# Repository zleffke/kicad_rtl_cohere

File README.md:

# KiCAD PCBs For RTL-SDR Coherent Receiver Projects
KiCAD projects for RTL-SDR coherency projects

## Board Descriptions
| Board | Description |
| --- | --- |
| clk_dist_4chan | 4 channel clock distribution |
| clk_dist_8chan | 8 channel clock distribution |
| external_clock | External clock interface to RTL-SDR V3 header |
| rf_split | 4 channel rf splitter for calibration noise distribution, two versions |

### Credit where its due!
This project is heavily inspired by the awesome work at [coherent-receiver.com](https://coherent-receiver.com).
I plan to make use of some common features, but also plan to do my own customized PCB layouts.
My work will be nowhere near as professional as theirs.
I highly recommend interested readers check out their page.

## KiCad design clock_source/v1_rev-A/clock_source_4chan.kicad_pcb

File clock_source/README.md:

# Clock Source Board
For coherent RTL-SDR projects.  
Based on Temperature Controlled Crystal Oscillator (TCXO).  
4 Channel Clock source (fanout) board
28.8 MHz clock frequency to RTL-SDR V3.

## V1 - 4 Channel Clock Source
- TCXO:  [Connor Winfield B31 28.8 MHz TCXO](http://www.conwin.com/datasheets/tx/tx415.pdf).
  - +-500 ppb
  - 2.0x2.5 mm footprint
  - digikey:  https://www.digikey.com/en/products/detail/connor-winfield/B31-028-8M/10296363
  
- SN74LVC2G14 buffer.  Matches ~10kOhm impedance of TCXO to 50 Ohm impedance of 5PB1104PGxx,
- Based on the 5PB1104PGxx Clock fanout buffer.
- UFL Connectors, to match the external clock interface board of the RTL SDR V3.
- Integrated 35 MHz LPFs on out and bypassable LPF on input.

### Rev-A, 20220314
Rectified deficiencies identified in Rev-.

### Rev-, 20220304
Forgot two key components:
- AC coupling capacitor at output of TCXO circuit.
- Resistor in parallel across input/output of SN74LVC2G14.
- Tested with razor blade / blue wire version of board.

### REMINDER! Credit where its due!
This project is heavily inspired by the awesome work at [coherent-receiver.com](https://coherent-receiver.com).

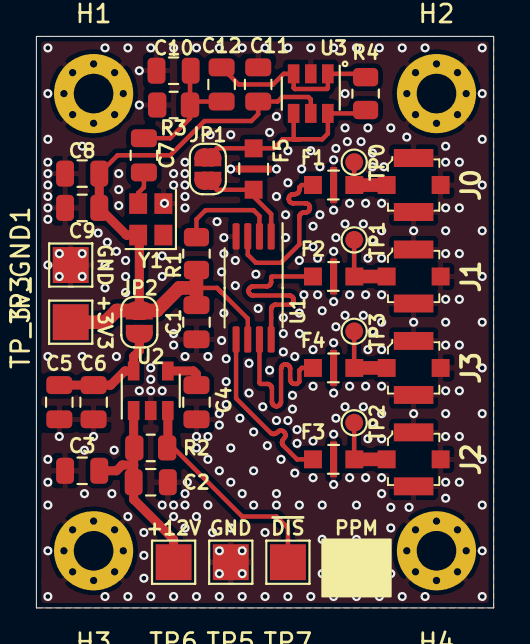
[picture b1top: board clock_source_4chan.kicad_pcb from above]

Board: 2 copper layers, 25.4 x 31.8 mm, 44 parts (0 on the bottom side), 20 nets.

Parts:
C1, C3, C4, C6, C8, C11: 0.1uF; C_0805_2012Metric
C2: 1uF; C_0805_2012Metric
C5: 10uF; C_0805_2012Metric
C7, C12: 1000pF; C_0805_2012Metric
C9: 0.01uF; C_0805_2012Metric
C10: 10pF; C_0805_2012Metric
F1, F2, F3, F4, F5: MEM2012S35R0T001; 0805_3PC_Pad
H1, H2, H3, H4: MountingHole_Pad; MountingHole_2.2mm_M2_Pad_Via
J0: Y0; Molex_734120114_UMC_RF_CONN_Vertical
J1: Y1; Molex_734120114_UMC_RF_CONN_Vertical
J2: Y2; Molex_734120114_UMC_RF_CONN_Vertical
J3: Y3; Molex_734120114_UMC_RF_CONN_Vertical
JP1: CLKIN_FILT_BYPASS; SolderJumper-2_P1.3mm_Open_RoundedPad1.0x1.5mm
JP2: VREG; SolderJumper-2_P1.3mm_Open_RoundedPad1.0x1.5mm
R1, R2: 100k; R_0805_2012Metric
R3, R4: 10k; R_0805_2012Metric
TP0, TP1, TP2, TP3: TestPoint; TestPoint_Pad_D1.0mm
TP5, TP6, TP7: TestPoint; TestPoint_Pad_2.0x2.0mm
TP_3v3: TestPoint; TestPoint_Pad_2.0x2.0mm
TP_GND1: TestPoint; TestPoint_Pad_2.0x2.0mm
U1: 5PB1104PGxx; TSSOP-8_4.4x3mm_P0.65mm
U2: SPX3819M5-L-3-3; SOT-23-5
U3: SN74LVC2G14DBV; SOT-23-6
Y1: TCXO_B31; Crystal_SMD_2520-4Pin_2.5x2.0mm

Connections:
+3V3: C1.2, C8.1, C9.1, C11.1, JP2.2, R1.2, TP_3v3.1, U1.6, U3.5, Y1.4
+12V: C2.1, C3.1, R2.1, TP6.1, U2.1
/Y0: F1.1, U1.3
/Y1: F2.1, U1.8
/Y2: F3.1, U1.5
/Y3: F4.1, U1.7
GND: C1.1, C2.2, C3.2, C4.2, C5.2, C6.2, C8.2, C9.2, C10.2, C11.2, F1.3, F2.3, F3.3, F4.3, F5.3, H1.1, H2.1, H3.1, H4.1, J0.1, J1.1, J2.1, J3.1, R3.2, TP5.1, TP_GND1.1, U1.4, U2.2, U3.2, Y1.2
unnamed: C4.1, U2.4
unnamed: C5.1, C6.1, JP2.1, U2.5
unnamed: C7.1, Y1.3
unnamed: C7.2, C10.1, C12.2, R3.1
unnamed: C12.1, R4.2, U3.1, U3.3
unnamed: F1.2, J0.2, TP0.1
unnamed: F2.2, J1.2, TP1.1
unnamed: F3.2, J2.2, TP2.1
unnamed: F4.2, J3.2, TP3.1
unnamed: F5.1, JP1.1, R4.1, U3.4, U3.6
unnamed: F5.2, JP1.2, U1.1
unnamed: R1.1, U1.2
unnamed: R2.2, TP7.1, U2.3

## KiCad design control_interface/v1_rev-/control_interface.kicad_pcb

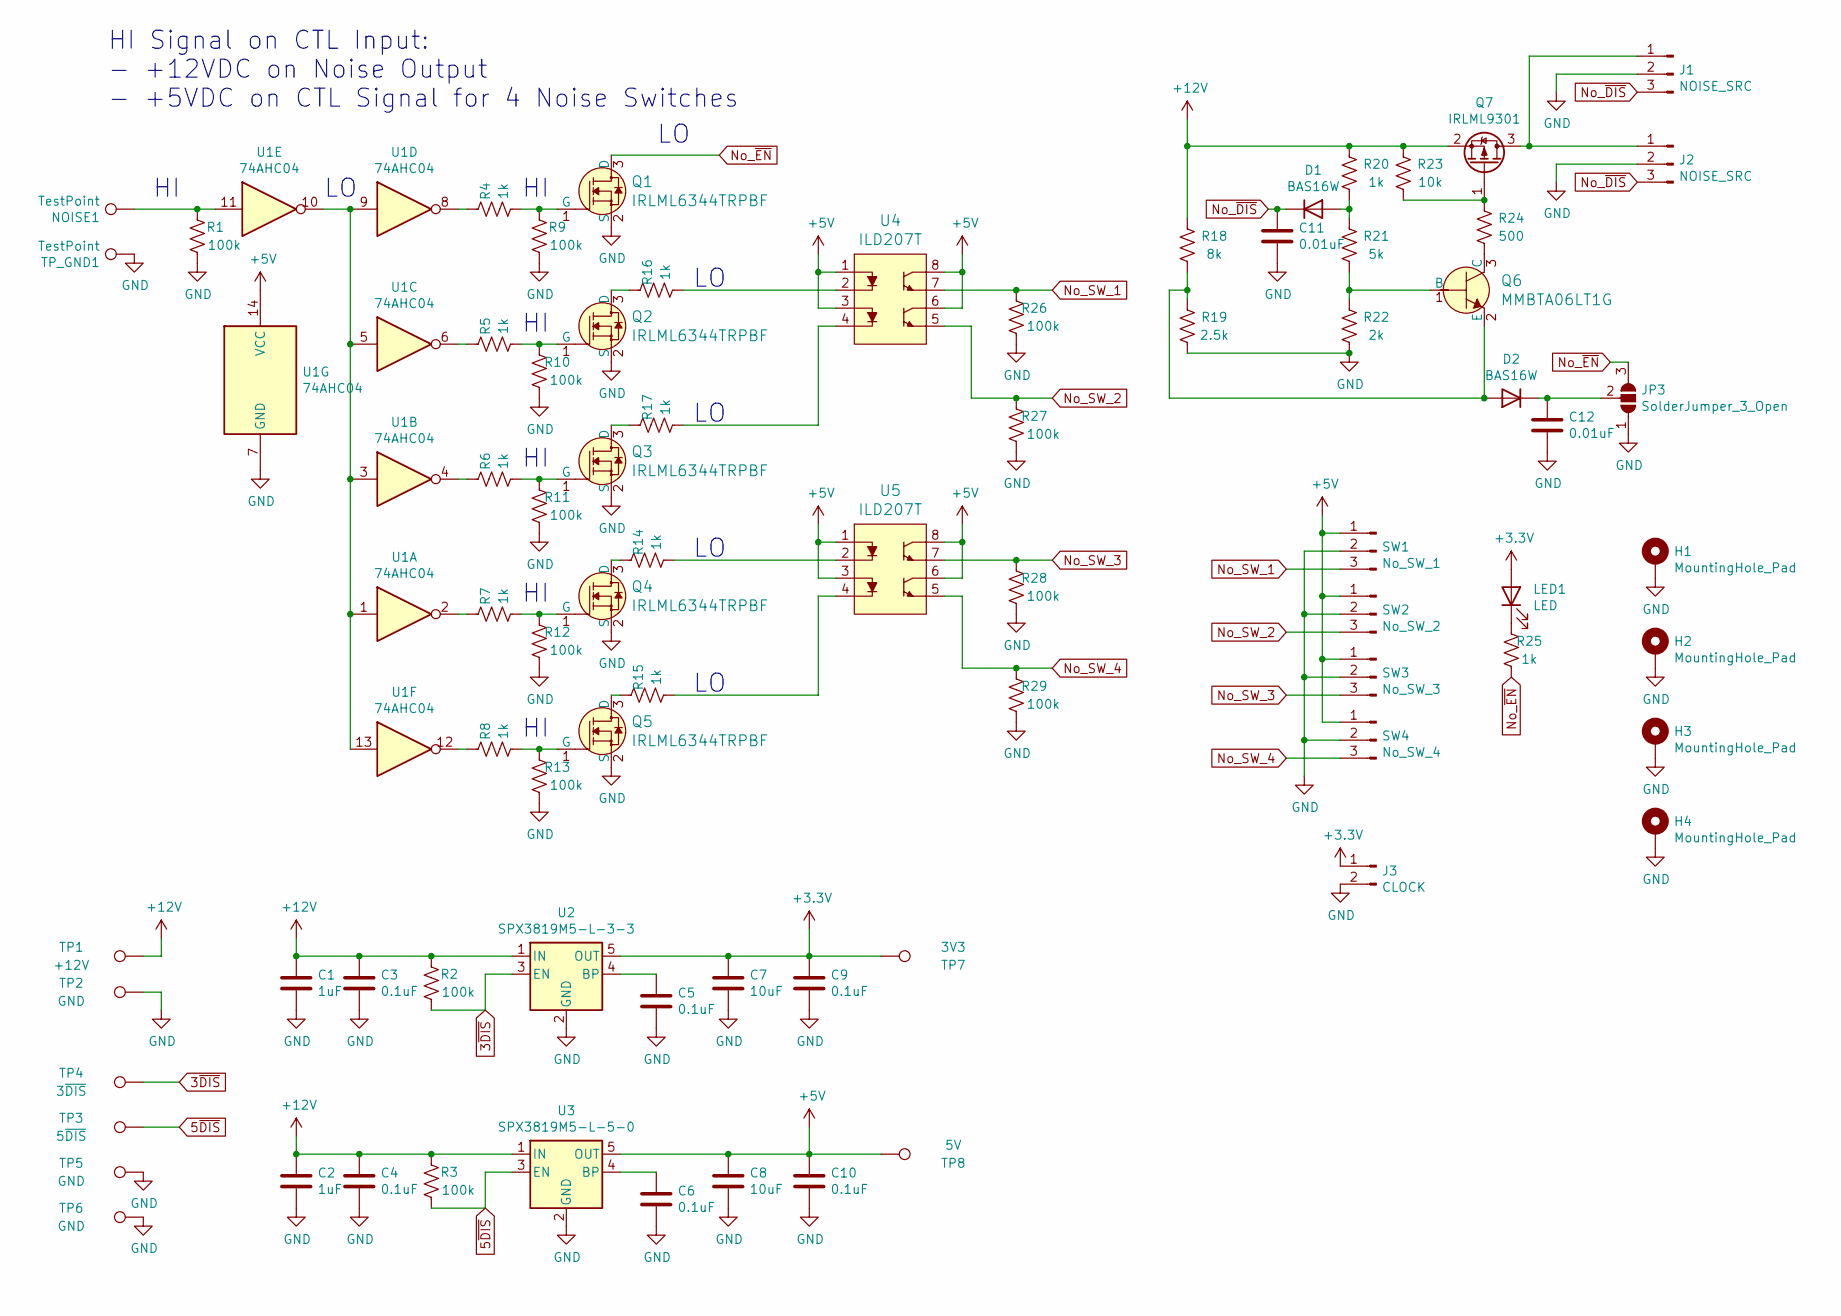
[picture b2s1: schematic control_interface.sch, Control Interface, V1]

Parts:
C1, C2: 1uF; C_0805_2012Metric
C3, C4, C5, C6, C9, C10: 0.1uF; C_0805_2012Metric
C7, C8: 10uF; C_0805_2012Metric
C11, C12: 0.01uF; C_0805_2012Metric
D1, D2: BAS16W; SOT-323_SC-70
H1, H2, H3, H4: MountingHole_Pad; MountingHole_2.2mm_M2_Pad_Via
J1, J2: NOISE_SRC; PinHeader_1x03_P2.54mm_Vertical
J3: CLOCK; PinHeader_1x02_P2.54mm_Vertical
JP3: SolderJumper_3_Open; SolderJumper-3_P1.3mm_Open_RoundedPad1.0x1.5mm_NumberLabels
LED1: LED; LED_0805_2012Metric
NOISE1: TestPoint; TestPoint_Pad_2.0x2.0mm
Q1, Q2, Q3, Q4, Q5: IRLML6344TRPBF; SOT-23-3; MPN IRLML6344TRPBF; Digi-Key_PN IRLML6344TRPBFCT-ND
Q6: MMBTA06LT1G; SOT-23-3; MPN MMBTA06LT1G; Digi-Key_PN MMBTA06LT1GOSCT-ND
Q7: IRLML9301; SOT-23-3
R1, R2, R3, R9, R10, R11, R12, R13, R26, R27, R28, R29: 100k; R_0805_2012Metric
R4, R5, R6, R7, R8, R14, R15, R16, R17, R20, R25: 1k; R_0805_2012Metric
R18: 8k; R_0805_2012Metric
R19: 2.5k; R_0805_2012Metric
R21: 5k; R_0805_2012Metric
R22: 2k; R_0805_2012Metric
R23: 10k; R_0805_2012Metric
R24: 500; R_0805_2012Metric
SW1: No_SW_1; PinHeader_1x03_P2.54mm_Vertical
SW2: No_SW_2; PinHeader_1x03_P2.54mm_Vertical
SW3: No_SW_3; PinHeader_1x03_P2.54mm_Vertical
SW4: No_SW_4; PinHeader_1x03_P2.54mm_Vertical
TP1: +12V; TestPoint_Pad_2.0x2.0mm
TP2, TP5, TP6: GND; TestPoint_Pad_2.0x2.0mm
TP3: 5~DIS; TestPoint_Pad_2.0x2.0mm
TP4: 3~DIS; TestPoint_Pad_2.0x2.0mm
TP7: 3V3; TestPoint_Pad_2.0x2.0mm
TP8: 5V; TestPoint_Pad_2.0x2.0mm
TP_GND1: TestPoint; TestPoint_Pad_2.0x2.0mm
U1: 74AHC04; SOIC-14_W3.9mm
U2: SPX3819M5-L-3-3; SOT-23-5
U3: SPX3819M5-L-5-0; SOT-23-5
U4, U5: ILD207T; SOIC-8_W3.9mm; MPN ILD207T; Digi-Key_PN 751-1310-1-ND

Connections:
3~DIS: R2.2, TP4.1, U2.3 (EN)
5~DIS: R3.2, TP3.1, U3.3 (EN)
+3V3: C7.1, C9.1, J3.1, LED1.2 (A), TP7.1, U2.5 (OUT)
+5V: C8.1, C10.1, SW1.1, SW2.1, SW3.1, SW4.1, TP8.1, U1.14 (VCC), U3.5 (OUT), U4.1, U4.3, U4.6, U4.8, U5.1, U5.3, U5.6, U5.8
+12V: C1.1, C2.1, C3.1, C4.1, Q7.2 (S), R2.1, R3.1, R18.1, R20.1, R23.1, TP1.1, U2.1 (IN), U3.1 (IN)
GND: C1.2, C2.2, C3.2, C4.2, C5.2, C6.2, C7.2, C8.2, C9.2, C10.2, C11.2, C12.2, H1.1, H2.1, H3.1, H4.1, J1.2, J2.2, J3.2, JP3.1 (A), Q1.2 (S), Q2.2 (S), Q3.2 (S), Q4.2 (S), Q5.2 (S), R1.2, R9.2, R10.2, R11.2, R12.2, R13.2, R19.2, R22.2, R26.2, R27.2, R28.2, R29.2, SW1.2, SW2.2, SW3.2, SW4.2, TP2.1, TP5.1, TP6.1, TP_GND1.1, U1.7 (GND), U2.2 (GND), U3.2 (GND)
unnamed: C5.1, U2.4 (BP)
unnamed: C6.1, U3.4 (BP)
unnamed: C12.1, D2.3 (K), JP3.2 (C)
unnamed: D1.1 (A), R20.2, R21.1
unnamed: D2.1 (A), Q6.2 (E), R18.2, R19.1
unnamed: J1.1, J2.1, Q7.3 (D)
unnamed: LED1.1 (K), R25.1
unnamed: NOISE1.1, R1.1, U1.11
unnamed: Q1.1 (G), R4.2, R9.1
unnamed: Q2.1 (G), R5.2, R10.1
unnamed: Q2.3 (D), R16.1
unnamed: Q3.1 (G), R6.2, R11.1
unnamed: Q3.3 (D), R17.1
unnamed: Q4.1 (G), R7.2, R12.1
unnamed: Q4.3 (D), R14.1
unnamed: Q5.1 (G), R8.2, R13.1
unnamed: Q5.3 (D), R15.1
unnamed: Q6.1 (B), R21.2, R22.1
unnamed: Q6.3 (C), R24.2
unnamed: Q7.1 (G), R23.2, R24.1
unnamed: R4.1, U1.8
unnamed: R5.1, U1.6
unnamed: R6.1, U1.4
unnamed: R7.1, U1.2
unnamed: R8.1, U1.12
unnamed: R14.2, U5.2
unnamed: R15.2, U5.4
unnamed: R16.2, U4.2
unnamed: R17.2, U4.4
unnamed: U1.1, U1.3, U1.5, U1.9, U1.10, U1.13
No_SW_1: R26.1, SW1.3, U4.7
No_SW_2: R27.1, SW2.3, U4.5
No_SW_3: R28.1, SW3.3, U5.7
No_SW_4: R29.1, SW4.3, U5.5
No_~DIS: C11.1, D1.3 (K), J1.3, J2.3
No_~EN: JP3.3 (B), Q1.3 (D), R25.2

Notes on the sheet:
HI Signal on CTL Input: - +12VDC on Noise Output - +5VDC on CTL Signal for 4 Noise Switches

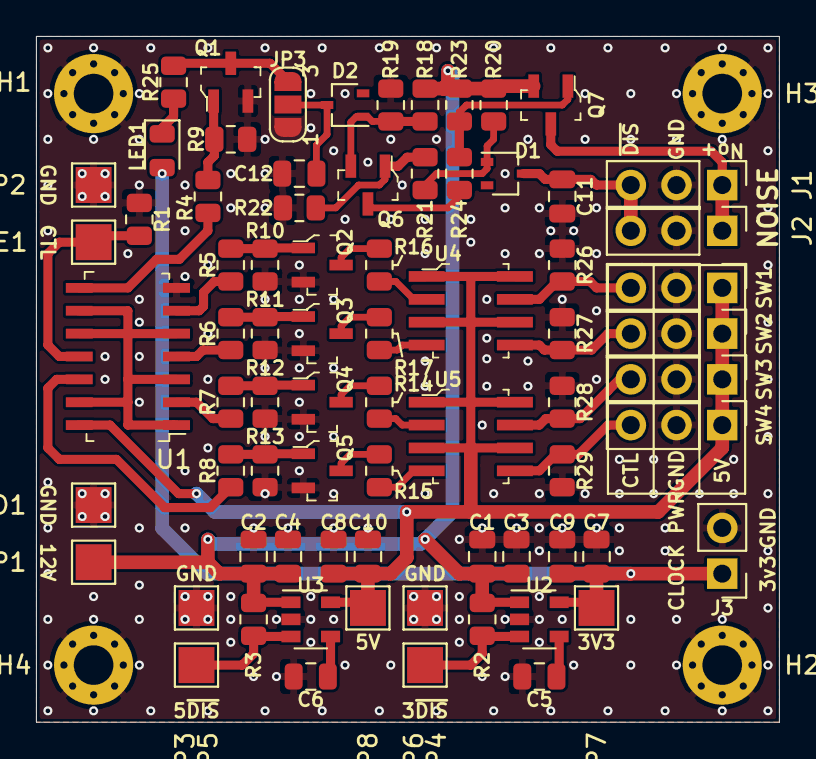
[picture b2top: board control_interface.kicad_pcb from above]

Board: 2 copper layers, 41.3 x 38.1 mm, 78 parts (0 on the bottom side), 42 nets.

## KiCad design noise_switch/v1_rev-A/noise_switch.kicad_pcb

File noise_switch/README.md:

# KiCAD PCBs For RTL-SDR Coherent Receiver Projects
Noise injection switch.  For injecting noise calibration signal into receive path.

## Board Descriptions
| Board | Description |
| --- | --- |
| V2, REV-  | Absorbative Switch.  MASW-007935-TR3000 design (uses SOT26 footprint).  Includes fix for SMA Connectors. |
| V1, REV-A | Reflective Switch.  MASWSS0136 design (uses SC70-6 footprint).  Fixed SMA Connector footprint to expose more copper. Update DC block capacitors to 1000pf.|
| V1, REV-  | Reflective Switch.  MASWSS0136 design (uses SC70-6 footprint) |

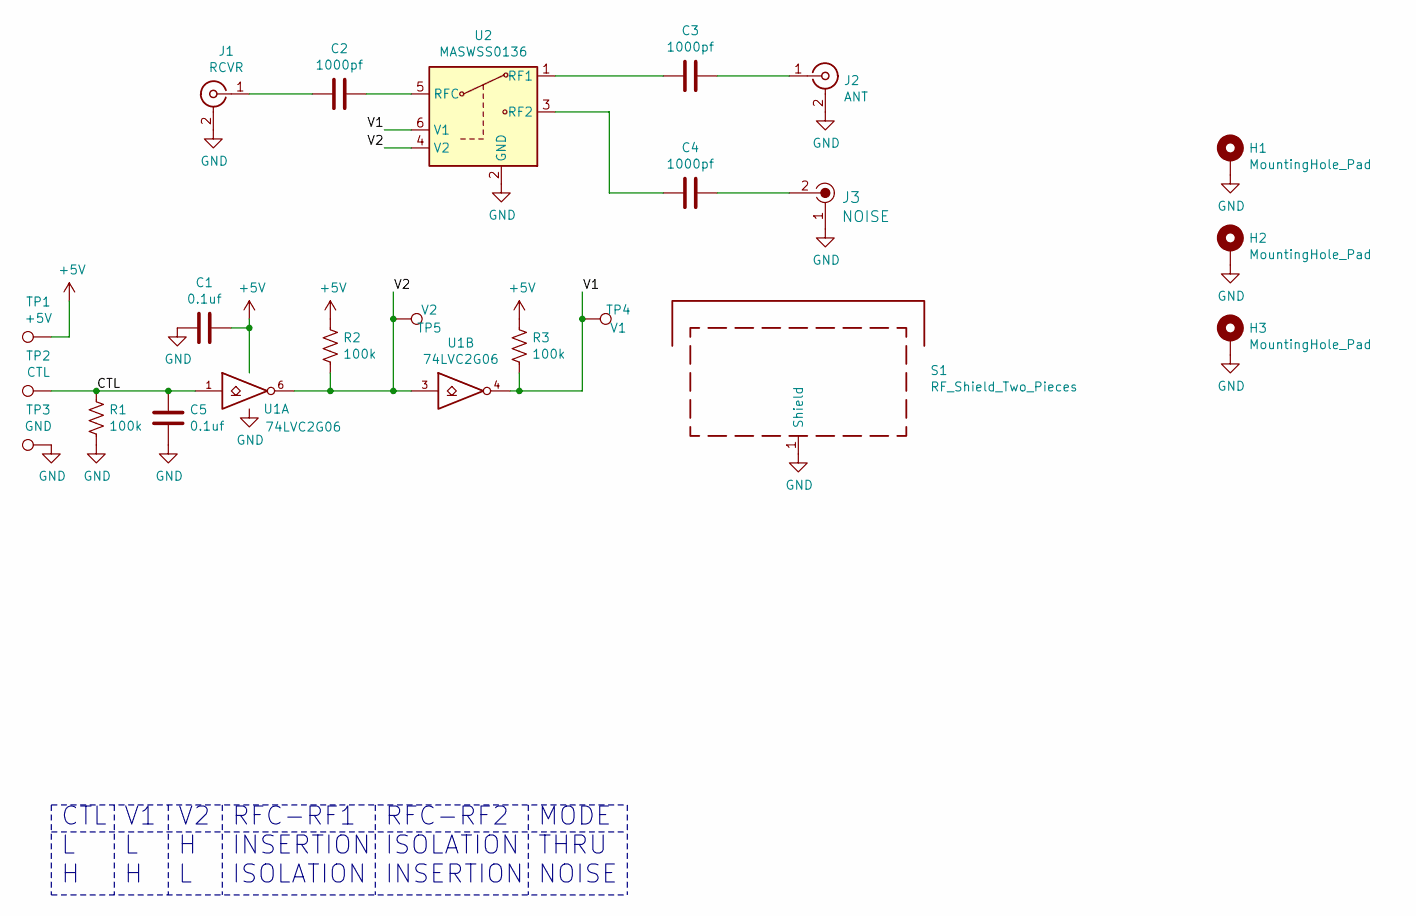
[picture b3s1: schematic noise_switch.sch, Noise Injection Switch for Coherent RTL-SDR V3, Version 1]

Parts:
C1, C5: 0.1uf; 0805
C2, C3, C4: 1000pf; 0805
H1, H2, H3: MountingHole_Pad; MountingHole_2.2mm_M2_Pad_Via
J1: RCVR; CONSMA013.062
J2: ANT; CONSMA003.062
J3: NOISE; Molex_734120114_UMC_RF_CONN_Vertical; MPN 0734120114; Digi-Key_PN WM3894CT-ND
R1, R2, R3: 100k; 0805
S1: RF_Shield_Two_Pieces; Wuerth_36103205_20x20mm
TP1: +5V; TestPoint_Pad_2.5x2.5mm
TP2: CTL; TestPoint_Pad_2.5x2.5mm
TP3: GND; TestPoint_Pad_2.5x2.5mm
TP4: V1; TestPoint_Pad_D1.5mm
TP5: V2; TestPoint_Pad_D1.5mm
U1: 74LVC2G06; SOT-363_SC-70-6
U2: MASWSS0136; SOT-363_SC-70-6

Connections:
+5V: C1.1, R2.1, R3.1, TP1.1, U1.5 (VCC)
/CTL: C5.2, R1.1, TP2.1, U1.1
/V1: R3.2, TP4.1, U1.4, U2.6 (V1)
/V2: R2.2, TP5.1, U1.3, U1.6, U2.4 (V2)
GND: C1.2, C5.1, H1.1, H2.1, H3.1, J1.2 (Ext), J2.2 (Ext), J3.1, R1.2, S1.1, TP3.1, U1.2 (GND), U2.2 (GND)
unnamed: C2.1, U2.5 (RFC)
unnamed: C2.2, J1.1 (In)
unnamed: C3.1, J2.1 (In)
unnamed: C3.2, U2.1 (RF1)
unnamed: C4.1, J3.2
unnamed: C4.2, U2.3 (RF2)

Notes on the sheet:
V2 H L
RFC-RF1 INSERTION ISOLATION
RFC-RF2 ISOLATION INSERTION
CTL L H
V1 L H
MODE THRU NOISE

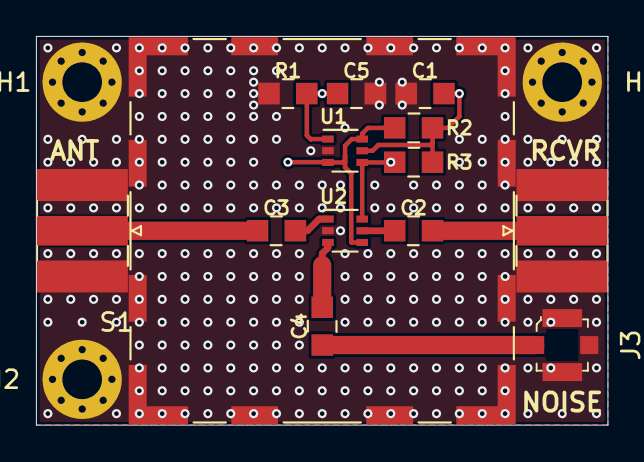
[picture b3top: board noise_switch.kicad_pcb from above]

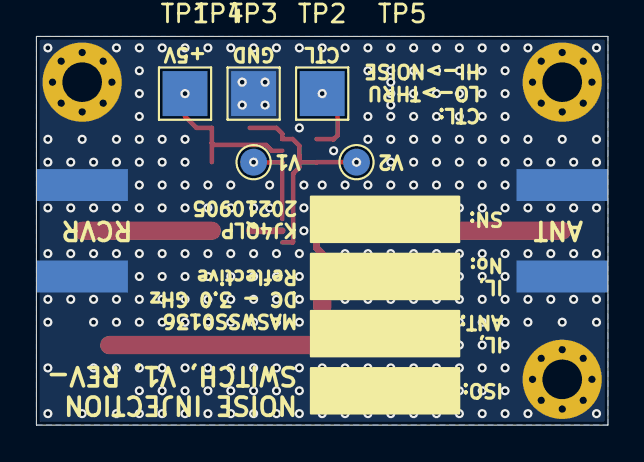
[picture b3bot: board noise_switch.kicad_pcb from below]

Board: 2 copper layers, 31.8 x 21.6 mm, 22 parts (5 on the bottom side), 11 nets.

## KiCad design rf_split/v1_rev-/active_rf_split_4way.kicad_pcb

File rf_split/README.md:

# Active RF Splitter Board Designs
- Primary use: distributing noise calibration source
- Given primary use, must try to control amplitude and phase to be equal on all outputs.
- Active because we are using RF amplifiers to overcome splitter losses.
  
## Board Versions

### Version 1 - Wye splitter
- based on 4-way Wye resistive splitter configuration
  - wye splitter is lossy, burns up half the power in the resistors.
  - 12dB loss from splitter input to output (for 4 channel).
- Active 4 channel noise distribution.
- BGA2815 RF amplifier from NXP (first time trying).

### Version 2 - Minicircuits splitter
- Nearly identical to Version 1, but based on cascaded minicircuits [TCP-2-25X+](https://www.minicircuits.com/WebStore/dashboard.html?model=TCP-2-25X%2B) rf splitter.
- Active 4 channel noise distribution.
- BGA2815 RF amplifier from NXP (first time trying).

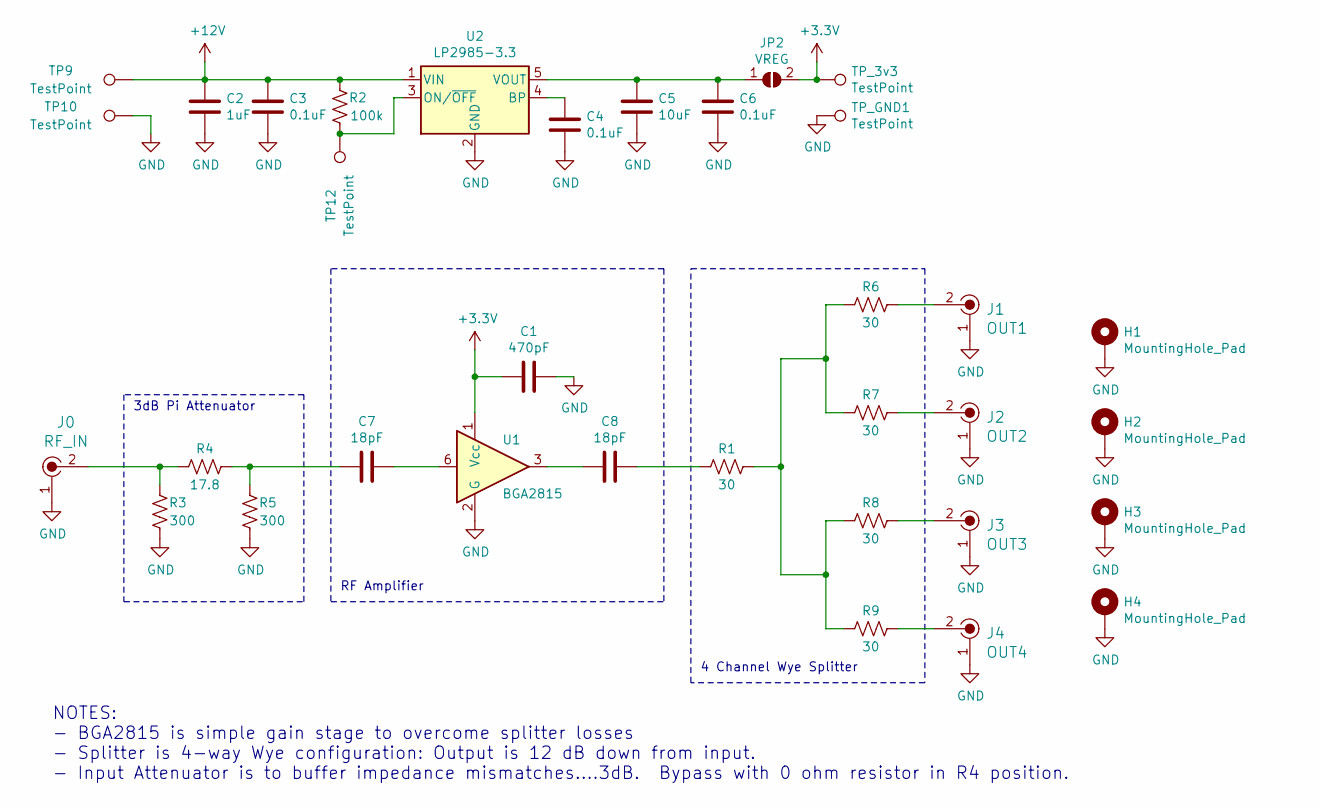
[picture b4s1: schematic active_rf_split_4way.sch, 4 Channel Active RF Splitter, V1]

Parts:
C1: 470pF; C_0805_2012Metric
C2: 1uF; C_0805_2012Metric
C3, C4, C6: 0.1uF; C_0805_2012Metric
C5: 10uF; C_0805_2012Metric
C7, C8: 18pF; C_0805_2012Metric
H1, H2, H3, H4: MountingHole_Pad; MountingHole_2.2mm_M2_Pad_Via
J0: RF_IN; Molex_734120114_UMC_RF_CONN_Vertical; MPN 0734120114; Digi-Key_PN WM3894CT-ND
J1: OUT1; Molex_734120114_UMC_RF_CONN_Vertical; MPN 0734120114; Digi-Key_PN WM3894CT-ND
J2: OUT2; Molex_734120114_UMC_RF_CONN_Vertical; MPN 0734120114; Digi-Key_PN WM3894CT-ND
J3: OUT3; Molex_734120114_UMC_RF_CONN_Vertical; MPN 0734120114; Digi-Key_PN WM3894CT-ND
J4: OUT4; Molex_734120114_UMC_RF_CONN_Vertical; MPN 0734120114; Digi-Key_PN WM3894CT-ND
JP2: VREG; SolderJumper-2_P1.3mm_Open_RoundedPad1.0x1.5mm
R1, R6, R7, R8, R9: 30; R_0805_2012Metric
R2: 100k; R_0805_2012Metric
R3, R5: 300; R_0805_2012Metric
R4: 17.8; R_0805_2012Metric
TP9, TP10, TP12: TestPoint; TestPoint_Pad_2.0x2.0mm
TP_3v3: TestPoint; TestPoint_Pad_2.0x2.0mm
TP_GND1: TestPoint; TestPoint_Pad_2.0x2.0mm
U1: BGA2815; SOT-363_SC-70-6
U2: LP2985-3.3; SOT-23-5

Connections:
+3V3: C1.2, JP2.2 (B), TP_3v3.1, U1.1 (Vcc)
+12V: C2.1, C3.1, R2.1, TP9.1, U2.1 (VIN)
GND: C1.1, C2.2, C3.2, C4.2, C5.2, C6.2, H1.1, H2.1, H3.1, H4.1, J0.1, J1.1, J2.1, J3.1, J4.1, R3.2, R5.2, TP10.1, TP_GND1.1, U1.2 (G), U1.4 (G), U1.5 (G), U2.2 (GND)
unnamed: C4.1, U2.4 (BP)
unnamed: C5.1, C6.1, JP2.1 (A), U2.5 (VOUT)
unnamed: C7.1, U1.6
unnamed: C7.2, R4.2, R5.1
unnamed: C8.1, R1.1
unnamed: C8.2, U1.3
unnamed: J0.2, R3.1, R4.1
unnamed: J1.2, R6.2
unnamed: J2.2, R7.2
unnamed: J3.2, R8.2
unnamed: J4.2, R9.2
unnamed: R1.2, R6.1, R7.1, R8.1, R9.1
unnamed: R2.2, TP12.1, U2.3 (ON/~OFF~)

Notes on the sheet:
NOTES: - BGA2815 is simple gain stage to overcome splitter losses - Splitter is 4-way Wye configuration: Output is 12 dB down from input. - Input Attenuator is to buffer impedance mismatches....3dB. Bypass with 0 ohm resistor in R4 position.
4 Channel Wye Splitter
RF Amplifier
3dB Pi Attenuator

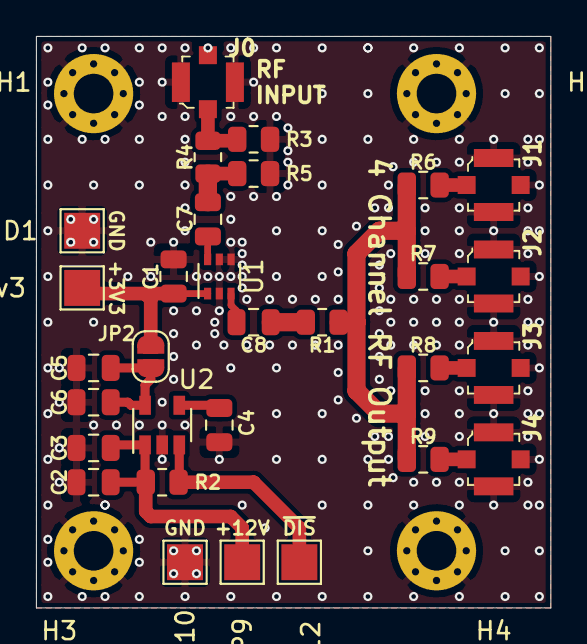
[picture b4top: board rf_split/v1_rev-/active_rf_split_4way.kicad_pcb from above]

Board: 2 copper layers, 28.6 x 31.8 mm, 34 parts (0 on the bottom side), 16 nets.

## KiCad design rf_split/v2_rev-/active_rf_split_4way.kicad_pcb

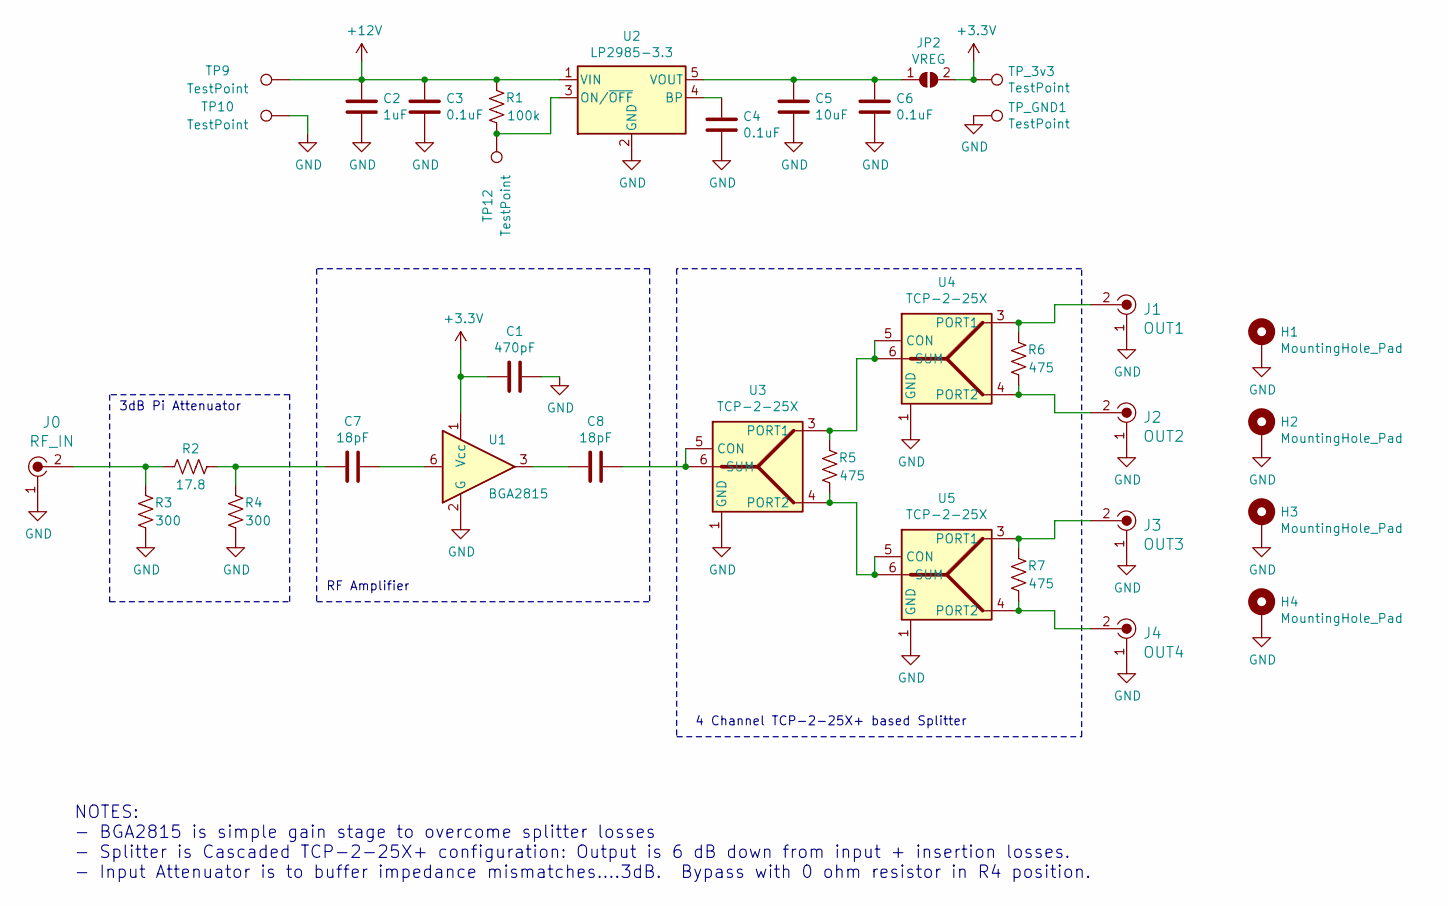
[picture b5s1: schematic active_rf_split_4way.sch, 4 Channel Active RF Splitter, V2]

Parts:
C1: 470pF; C_0805_2012Metric
C2: 1uF; C_0805_2012Metric
C3, C4, C6: 0.1uF; C_0805_2012Metric
C5: 10uF; C_0805_2012Metric
C7, C8: 18pF; C_0805_2012Metric
H1, H2, H3, H4: MountingHole_Pad; MountingHole_2.2mm_M2_Pad_Via
J0: RF_IN; Molex_734120114_UMC_RF_CONN_Vertical; MPN 0734120114; Digi-Key_PN WM3894CT-ND
J1: OUT1; Molex_734120114_UMC_RF_CONN_Vertical; MPN 0734120114; Digi-Key_PN WM3894CT-ND
J2: OUT2; Molex_734120114_UMC_RF_CONN_Vertical; MPN 0734120114; Digi-Key_PN WM3894CT-ND
J3: OUT3; Molex_734120114_UMC_RF_CONN_Vertical; MPN 0734120114; Digi-Key_PN WM3894CT-ND
J4: OUT4; Molex_734120114_UMC_RF_CONN_Vertical; MPN 0734120114; Digi-Key_PN WM3894CT-ND
JP2: VREG; SolderJumper-2_P1.3mm_Open_RoundedPad1.0x1.5mm
R1: 100k; R_0805_2012Metric
R2: 17.8; R_0805_2012Metric
R3, R4: 300; R_0805_2012Metric
R5, R6, R7: 475; R_0805_2012Metric
TP9, TP10, TP12: TestPoint; TestPoint_Pad_2.0x2.0mm
TP_3v3: TestPoint; TestPoint_Pad_2.0x2.0mm
TP_GND1: TestPoint; TestPoint_Pad_2.0x2.0mm
U1: BGA2815; SOT-363_SC-70-6
U2: LP2985-3.3; SOT-23-5
U3, U4, U5: TCP-2-25X; Mini-Circuits_DB1627

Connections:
+3V3: C1.2, JP2.2 (B), TP_3v3.1, U1.1 (Vcc)
+12V: C2.1, C3.1, R1.1, TP9.1, U2.1 (VIN)
GND: C1.1, C2.2, C3.2, C4.2, C5.2, C6.2, H1.1, H2.1, H3.1, H4.1, J0.1, J1.1, J2.1, J3.1, J4.1, R3.2, R4.2, TP10.1, TP_GND1.1, U1.2 (G), U1.4 (G), U1.5 (G), U2.2 (GND), U3.1 (GND), U4.1 (GND), U5.1 (GND)
unnamed: C4.1, U2.4 (BP)
unnamed: C5.1, C6.1, JP2.1 (A), U2.5 (VOUT)
unnamed: C7.1, U1.6
unnamed: C7.2, R2.2, R4.1
unnamed: C8.1, U3.2 (CON), U3.5 (CON), U3.6 (SUM)
unnamed: C8.2, U1.3
unnamed: J0.2, R2.1, R3.1
unnamed: J1.2, R6.1, U4.3 (PORT1)
unnamed: J2.2, R6.2, U4.4 (PORT2)
unnamed: J3.2, R7.1, U5.3 (PORT1)
unnamed: J4.2, R7.2, U5.4 (PORT2)
unnamed: R1.2, TP12.1, U2.3 (ON/~OFF~)
unnamed: R5.1, U3.3 (PORT1), U4.2 (CON), U4.5 (CON), U4.6 (SUM)
unnamed: R5.2, U3.4 (PORT2), U5.2 (CON), U5.5 (CON), U5.6 (SUM)

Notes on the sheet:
NOTES: - BGA2815 is simple gain stage to overcome splitter losses - Splitter is Cascaded TCP-2-25X+ configuration: Output is 6 dB down from input + insertion losses. - Input Attenuator is to buffer impedance mismatches....3dB. Bypass with 0 ohm resistor in R4 position.
4 Channel TCP-2-25X+ based Splitter
RF Amplifier
3dB Pi Attenuator

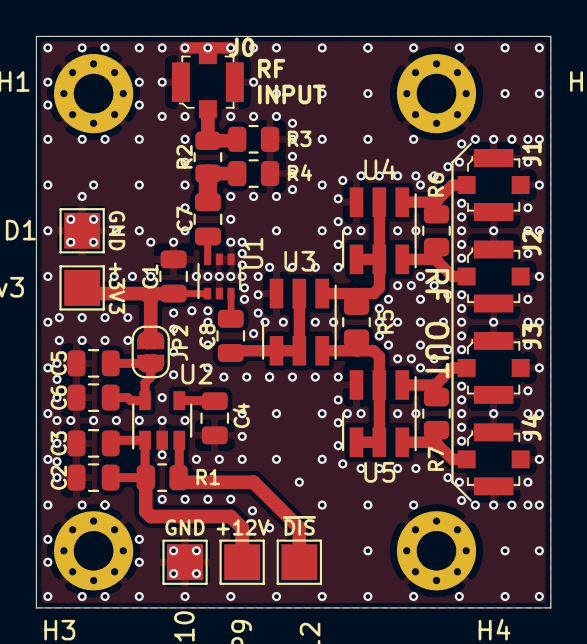
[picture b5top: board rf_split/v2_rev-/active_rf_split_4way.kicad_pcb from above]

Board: 2 copper layers, 28.6 x 31.8 mm, 35 parts (0 on the bottom side), 17 nets.

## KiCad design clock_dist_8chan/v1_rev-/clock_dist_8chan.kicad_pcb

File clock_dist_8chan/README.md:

# 8 Channel Clock Distribution Board
4 Channel Clock distribution (fanout) board for coherent RTL-SDR projects.
Intended for distributing 28.8 MHz clock frequency to RTL-SDR V3.

## V1
- Based on the 5PB1108PGxx IC.
- UFL Connectors, to match the external clock interface board of the RTL SDR V3.
- Integrated 35 MHz LPFs on out and bypassable LPF on input.
- V1, REV- subitted to Osh Park 20210320.

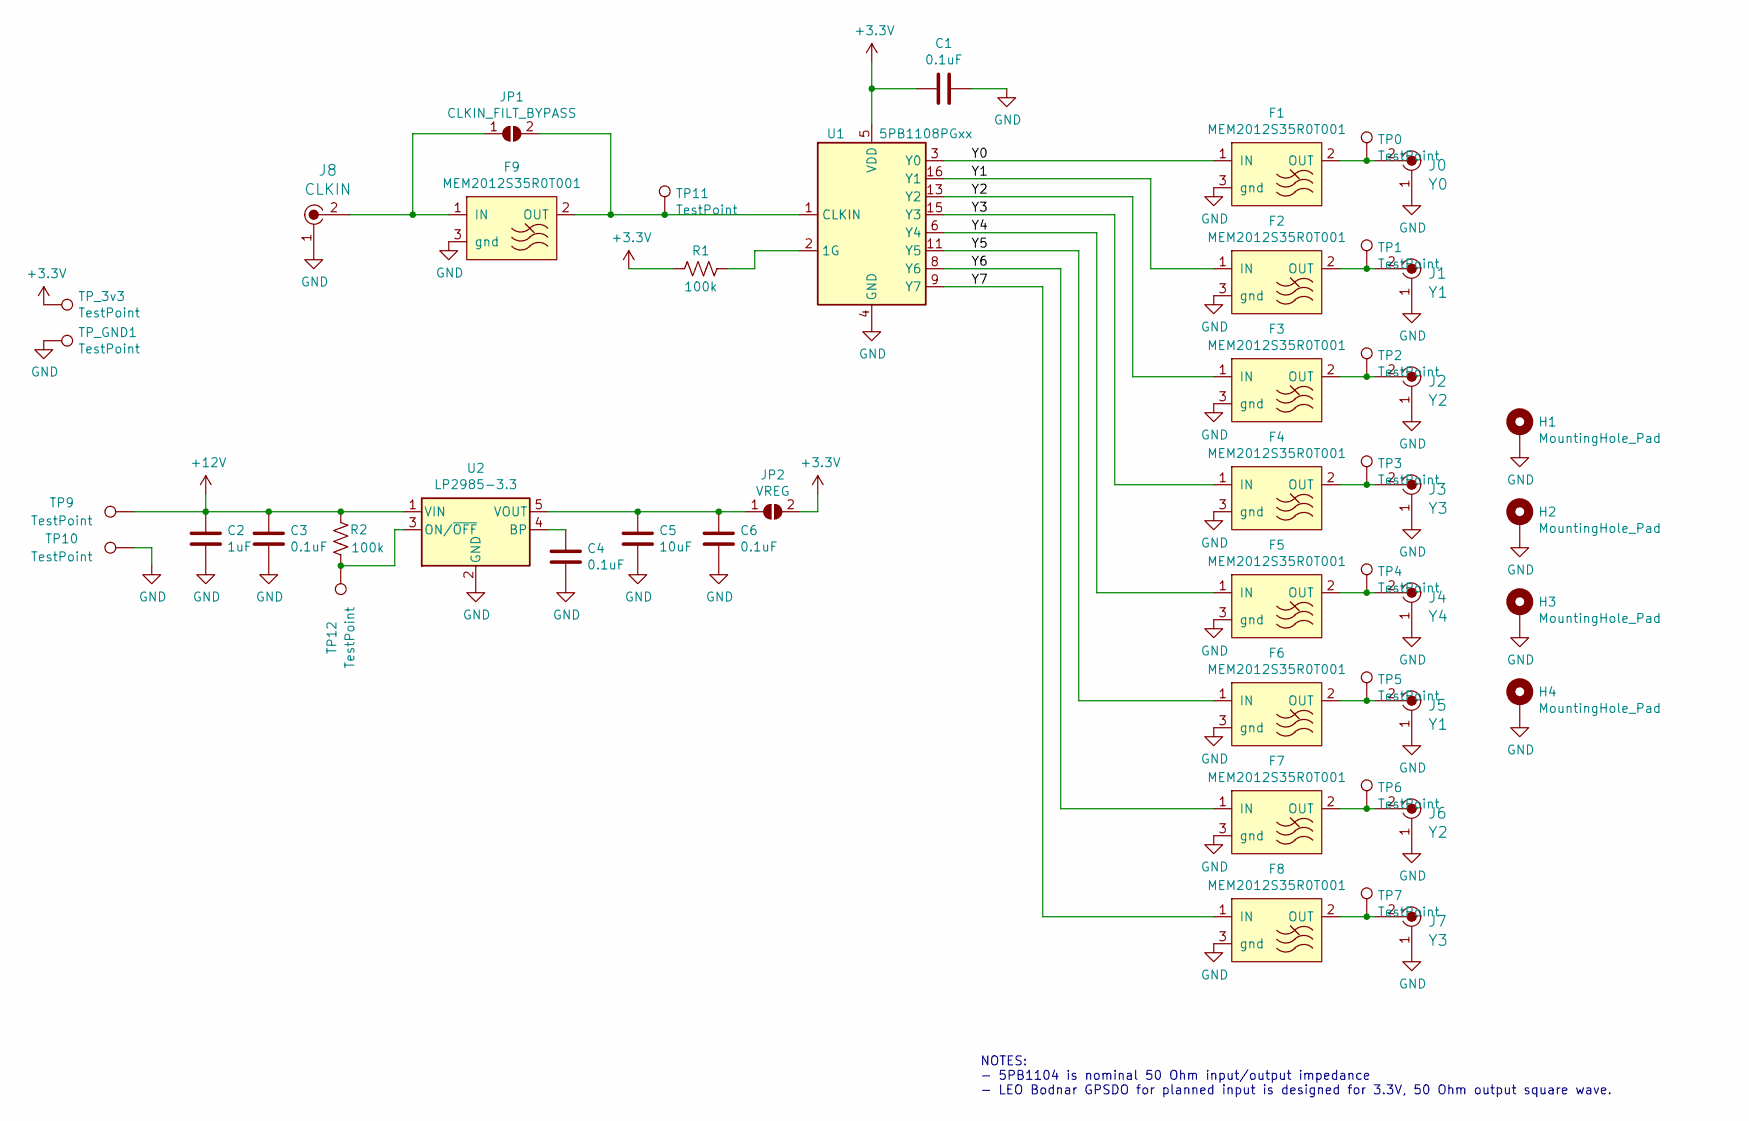
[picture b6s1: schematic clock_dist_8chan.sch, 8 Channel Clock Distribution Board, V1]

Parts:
C1, C3, C4, C6: 0.1uF; C_0805_2012Metric
C2: 1uF; C_0805_2012Metric
C5: 10uF; C_0805_2012Metric
F1, F2, F3, F4, F5, F6, F7, F8, F9: MEM2012S35R0T001; 0805_3PC_Pad
H1, H2, H3, H4: MountingHole_Pad; MountingHole_2.2mm_M2_Pad_Via
J0: Y0; Molex_734120114_UMC_RF_CONN_Vertical; MPN 0734120114; Digi-Key_PN WM3894CT-ND
J1, J5: Y1; Molex_734120114_UMC_RF_CONN_Vertical; MPN 0734120114; Digi-Key_PN WM3894CT-ND
J2, J6: Y2; Molex_734120114_UMC_RF_CONN_Vertical; MPN 0734120114; Digi-Key_PN WM3894CT-ND
J3, J7: Y3; Molex_734120114_UMC_RF_CONN_Vertical; MPN 0734120114; Digi-Key_PN WM3894CT-ND
J4: Y4; Molex_734120114_UMC_RF_CONN_Vertical; MPN 0734120114; Digi-Key_PN WM3894CT-ND
J8: CLKIN; Molex_734120114_UMC_RF_CONN_Vertical; MPN 0734120114; Digi-Key_PN WM3894CT-ND
JP1: CLKIN_FILT_BYPASS; SolderJumper-2_P1.3mm_Open_RoundedPad1.0x1.5mm
JP2: VREG; SolderJumper-2_P1.3mm_Open_RoundedPad1.0x1.5mm
R1, R2: 100k; R_0805_2012Metric
TP0, TP1, TP2, TP3, TP4, TP5, TP6, TP7, TP11: TestPoint; TestPoint_Pad_D1.0mm
TP9, TP10, TP12: TestPoint; TestPoint_Pad_2.0x2.0mm
TP_3v3: TestPoint; TestPoint_Pad_2.0x2.0mm
TP_GND1: TestPoint; TestPoint_Pad_2.0x2.0mm
U1: 5PB1108PGxx; TSSOP-16_4.4x5mm_P0.65mm
U2: LP2985-3.3; SOT-23-5

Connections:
+3V3: C1.2, JP2.2 (B), R1.1, TP_3v3.1, U1.5 (VDD), U1.10 (VDD), U1.14 (VDD)
+12V: C2.1, C3.1, R2.1, TP9.1, U2.1 (VIN)
/Y0: F1.1 (IN), U1.3 (Y0)
/Y1: F2.1 (IN), U1.16 (Y1)
/Y2: F3.1 (IN), U1.13 (Y2)
/Y3: F4.1 (IN), U1.15 (Y3)
/Y4: F5.1 (IN), U1.6 (Y4)
/Y5: F6.1 (IN), U1.11 (Y5)
/Y6: F7.1 (IN), U1.8 (Y6)
/Y7: F8.1 (IN), U1.9 (Y7)
GND: C1.1, C2.2, C3.2, C4.2, C5.2, C6.2, F1.3 (gnd), F2.3 (gnd), F3.3 (gnd), F4.3 (gnd), F5.3 (gnd), F6.3 (gnd), F7.3 (gnd), F8.3 (gnd), F9.3 (gnd), H1.1, H2.1, H3.1, H4.1, J0.1, J1.1, J2.1, J3.1, J4.1, J5.1, J6.1, J7.1, J8.1, TP10.1, TP_GND1.1, U1.4 (GND), U1.7 (GND), U1.12 (GND), U2.2 (GND)
unnamed: C4.1, U2.4 (BP)
unnamed: C5.1, C6.1, JP2.1 (A), U2.5 (VOUT)
unnamed: F1.2 (OUT), J0.2, TP0.1
unnamed: F2.2 (OUT), J1.2, TP1.1
unnamed: F3.2 (OUT), J2.2, TP2.1
unnamed: F4.2 (OUT), J3.2, TP3.1
unnamed: F5.2 (OUT), J4.2, TP4.1
unnamed: F6.2 (OUT), J5.2, TP5.1
unnamed: F7.2 (OUT), J6.2, TP6.1
unnamed: F8.2 (OUT), J7.2, TP7.1
unnamed: F9.1 (IN), J8.2, JP1.1 (A)
unnamed: F9.2 (OUT), JP1.2 (B), TP11.1, U1.1 (CLKIN)
unnamed: R1.2, U1.2 (1G)
unnamed: R2.2, TP12.1, U2.3 (ON/~OFF~)

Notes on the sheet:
NOTES: - 5PB1104 is nominal 50 Ohm input/output impedance - LEO Bodnar GPSDO for planned input is designed for 3.3V, 50 Ohm output square wave.

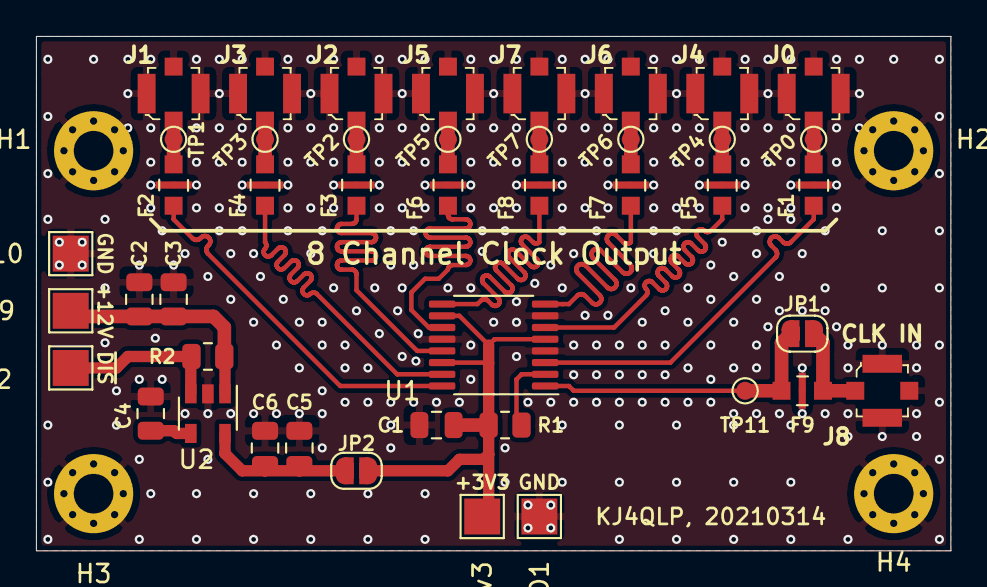
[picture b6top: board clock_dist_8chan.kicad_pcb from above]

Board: 2 copper layers, 50.8 x 28.6 mm, 48 parts (0 on the bottom side), 25 nets.

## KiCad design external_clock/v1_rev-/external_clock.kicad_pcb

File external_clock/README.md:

# External Clock Interface
External clock interface to RTL-SDR V3 header.

## V1
- UFL Connectors to 7 pin 2.0mm header of RTL-SDR V3.
- V1, REV- subitted to Osh Park 20210313

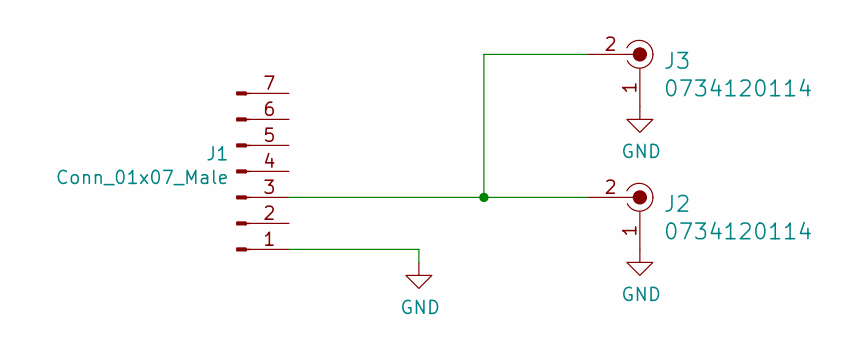
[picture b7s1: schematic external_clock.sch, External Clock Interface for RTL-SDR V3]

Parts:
J1: Conn_01x07_Male; PinHeader_1x07_P2.00mm_Horizontal
J2, J3: 0734120114; Molex_734120114_UMC_RF_CONN_Vertical; MPN 0734120114; Digi-Key_PN WM3894CT-ND

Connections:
GND: J1.1, J2.1, J3.1
unnamed: J1.3, J2.2, J3.2

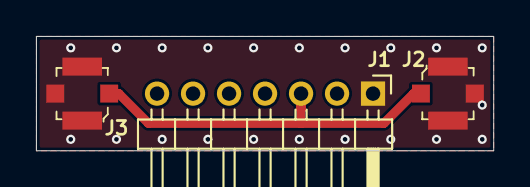
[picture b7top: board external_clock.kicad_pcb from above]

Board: 2 copper layers, 25.4 x 6.4 mm, 3 parts (0 on the bottom side), 2 nets.

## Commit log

2021-03-14 initial commit, submitted to osh park 20210313
2021-03-14 cleaned up files, added external clock readme
2021-03-15 initial commit of completed v1, rev-. This commit submitted to osk park 20210315.
2021-03-20 8 channel variant, v1, rev-, submitted to osh park 20210320.
2021-03-20 master BOM for coherent rtl-sdr parts....for multiple boards.
2021-03-21 updated readmes and fixed pcb page info
2021-03-21 update master parts list
2021-03-21 4way, wye, rf splitter board - submitted to osh park 20210321
2021-03-21 updaed readme
2021-03-21 aded second version of RF splitter. submitted to oshpark 20210320.
2021-03-21 updated master purchase list
2021-03-21 updated rf amp decoupling capacitor value
2021-04-10 adding pdf of schematics
2021-04-10 updated master parts list
2021-06-07 adding initial measurements.
2021-09-10 added noise injection switch v1, rev-, also updated BOM.
2021-09-11 added ufl to sma adapter
2021-09-21 updated BOM
2021-09-21 added noise switch SOT-23-6 variant, v2 rev-, sent to osh park. added v1, rev-A update, fixed SMA footprints.
2021-09-22 noise control interface board. Controls noise source and switches. V1, Rev-, sent to Osh Park.
2021-10-02 adding pdf of schematic
2021-10-03 Added noise switch measurements, v2, Rev- board, reflective switch
2021-10-03 rearranged measurement folder
2021-10-03 updated readme for measurements
2022-03-04 adding 4chan tcxo clock source board. this commit sent to osh park 20220304.
2022-03-15 revision-A. Submitted to osh park 20220314.
2022-03-16 adding new KiCAD 6 files.

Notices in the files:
clock_dist_8chan/v1_rev-/clock_dist_8chan.kicad_pcb:
License: CC BY 4.0
clock_dist_8chan/v1_rev-/clock_dist_8chan.sch:
creativecommons.org/licenses/by/4.0
